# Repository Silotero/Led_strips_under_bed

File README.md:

# Led_strips_under_bed
Led strips that lights up according to the output of distance sensors.

The project uses 8 of HC-SR04 ultrasonic distance sensors to measure the distance beetween a detected project. They are separated into 2 zones, 4 sensors each. The 2 zones are at a 90 deegre angle (on a corner). Appropriate leds on the 2 led strips light up according to the readout of the sensors. There are 4 zones according to the distance:
-more than 115 cm - nothing lights up
-beetween 85 cm and 115 cm - light up blue
-beetween 55 cm and 85 cm - light up green
-beetween 22 cm and 55 cm - light up red

Everything is controlled via Atmega328p. The led strips are of WS2813 type.

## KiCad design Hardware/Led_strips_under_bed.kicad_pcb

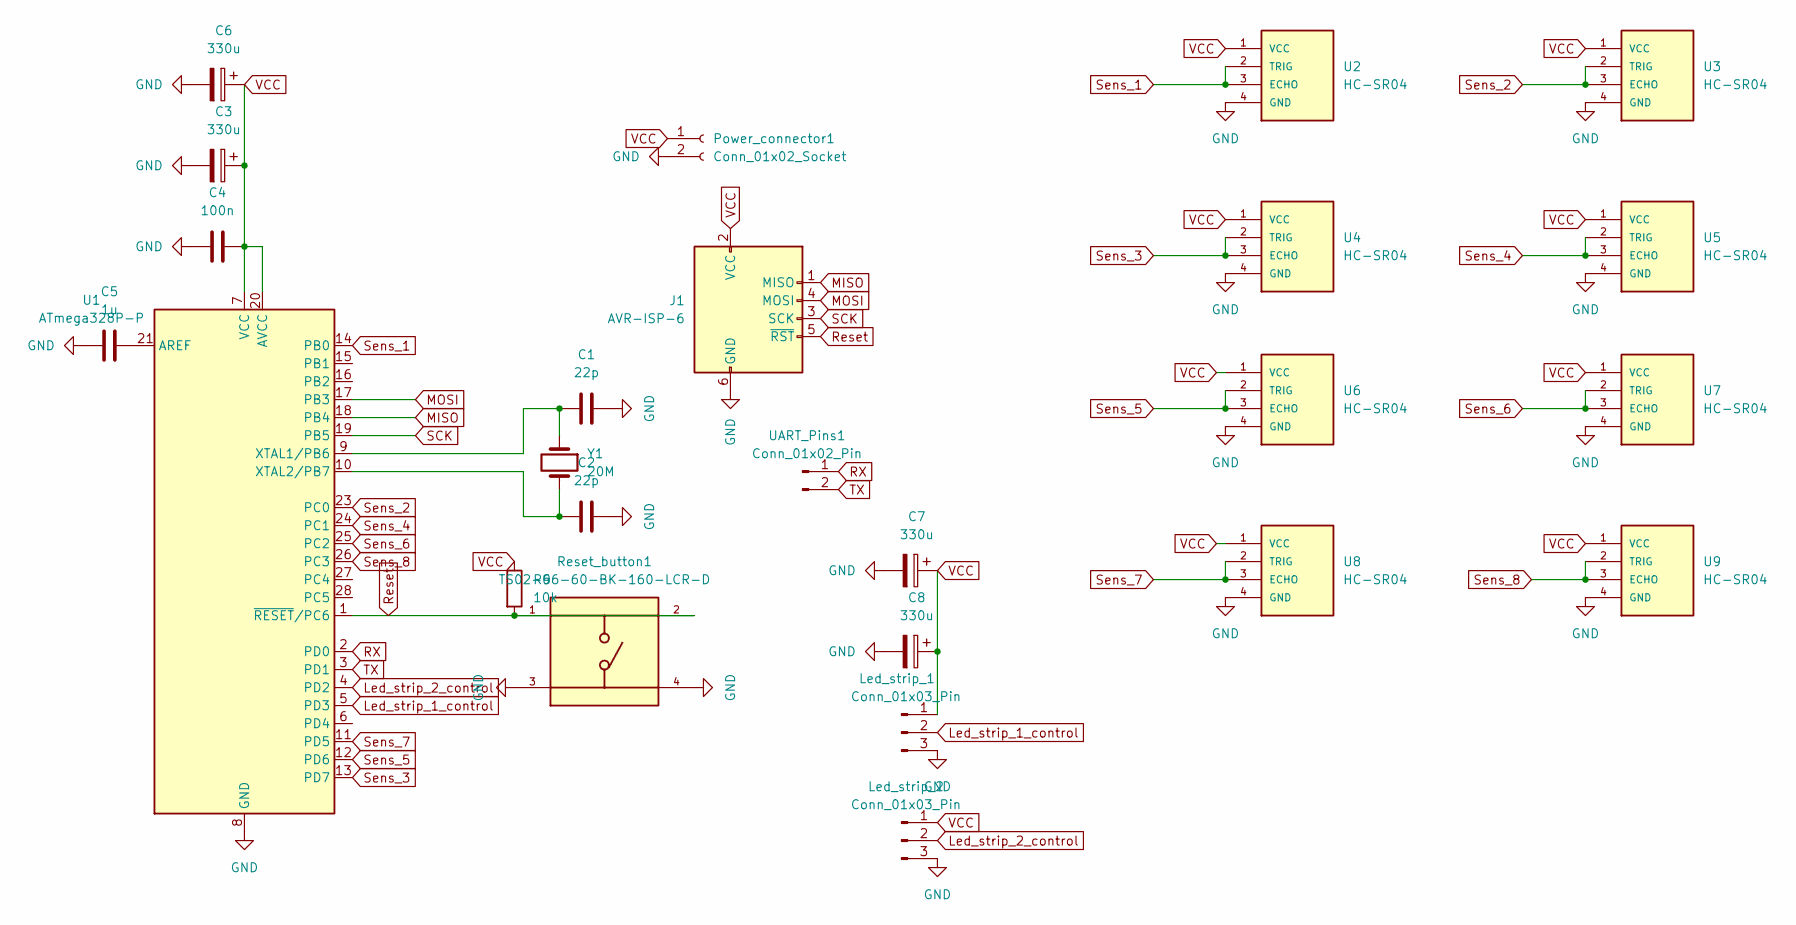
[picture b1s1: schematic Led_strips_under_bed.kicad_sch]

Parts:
C1, C2: 22p; C_0603_1608Metric
C3, C6, C7, C8: 330u; CP_Radial_D6.3mm_P2.50mm
C4: 100n; C_0603_1608Metric
C5: 1u; C_0603_1608Metric
J1: AVR-ISP-6; IDC-Header_2x03_P2.54mm_Vertical
Led_strip_1, Led_strip_2: Conn_01x03_Pin; PinHeader_1x03_P2.54mm_Vertical
Power_connector1: Conn_01x02_Socket; PinSocket_1x02_P2.54mm_Vertical
R9: 10k; R_0805_2012Metric
Reset_button1: TS02-66-60-BK-160-LCR-D; SW_TS02-66-60-BK-160-LCR-D; PARTREV 1.0
U1: ATmega328P-P; DIP-28_W7.62mm
U2, U3, U4, U5, U6, U7, U8, U9: HC-SR04; XCVR_HC-SR04
UART_Pins1: Conn_01x02_Pin; PinHeader_1x02_P2.54mm_Vertical
Y1: 20M; Resonator-2Pin_W7.0mm_H2.5mm

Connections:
GND: C1.2, C2.2, C3.2, C4.2, C5.2, C6.2, C7.2, C8.2, J1.6 (GND), Led_strip_1.3, Led_strip_2.3, Power_connector1.2, Reset_button1.3, Reset_button1.4, U1.8 (GND), U1.22 (GND), U2.4 (GND), U3.4 (GND), U4.4 (GND), U5.4 (GND), U6.4 (GND), U7.4 (GND), U8.4 (GND), U9.4 (GND); also elsewhere on the board
Led_strip_1_control: Led_strip_1.2, U1.5 (PD3)
Led_strip_2_control: Led_strip_2.2, U1.4 (PD2)
MISO: J1.1 (MISO), U1.18 (PB4)
MOSI: J1.4 (MOSI), U1.17 (PB3)
unnamed: C5.1, U1.21 (AREF)
unnamed: C1.1, U1.9 (XTAL1/PB6), Y1.1
unnamed: C2.1, U1.10 (XTAL2/PB7), Y1.2
RX: U1.2 (PD0), UART_Pins1.1
Reset: J1.5 (~RST), R9.2, Reset_button1.1, Reset_button1.2, U1.1 (~RESET/PC6); also elsewhere on the board
SCK: J1.3 (SCK), U1.19 (PB5)
Sens_1: U1.14 (PB0), U2.2 (TRIG), U2.3 (ECHO)
Sens_2: U1.23 (PC0), U3.2 (TRIG), U3.3 (ECHO)
Sens_3: U1.13 (PD7), U4.2 (TRIG), U4.3 (ECHO)
Sens_4: U1.24 (PC1), U5.2 (TRIG), U5.3 (ECHO)
Sens_5: U1.12 (PD6), U6.2 (TRIG), U6.3 (ECHO)
Sens_6: U1.25 (PC2), U7.2 (TRIG), U7.3 (ECHO)
Sens_7: U1.11 (PD5), U8.2 (TRIG), U8.3 (ECHO)
Sens_8: U1.26 (PC3), U9.2 (TRIG), U9.3 (ECHO)
TX: U1.3 (PD1), UART_Pins1.2
VCC: C3.1, C4.1, C6.1, C7.1, C8.1, J1.2 (VCC), Led_strip_1.1, Led_strip_2.1, Power_connector1.1, R9.1, U1.7 (VCC), U1.20 (AVCC), U2.1 (VCC), U3.1 (VCC), U4.1 (VCC), U5.1 (VCC), U6.1 (VCC), U7.1 (VCC), U8.1 (VCC), U9.1 (VCC)

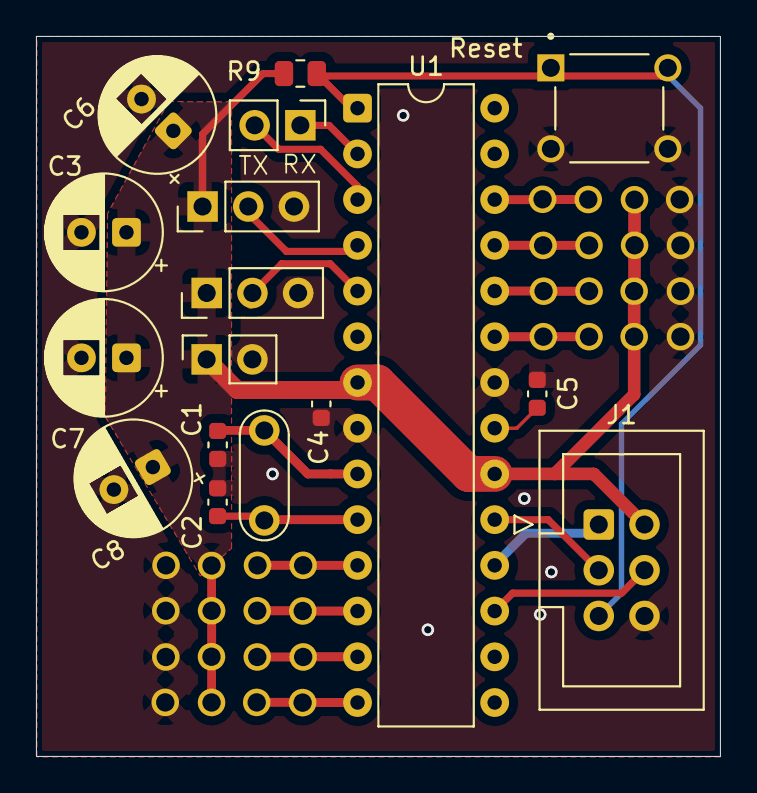
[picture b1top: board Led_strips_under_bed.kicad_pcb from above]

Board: 2 copper layers, 38.0 x 40.0 mm, 25 parts (0 on the bottom side), 21 nets.

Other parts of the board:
Reset: TS02-66-60-BK-160-LCR-D; SW_TS02-66-60-BK-160-LCR-D

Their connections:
GND: Reset.3, Reset.4; also elsewhere on the board
Reset: Reset.1, Reset.2; also elsewhere on the board

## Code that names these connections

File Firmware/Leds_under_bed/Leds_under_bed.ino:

#ifndef F_CPU
#define F_CPU 20000000UL
#endif
#include <avr/io.h>
#include <util/delay.h>
#include <stdbool.h>
#include <FastLED.h>
#include <UART_w_c.h>
#include <stdio.h>

#define NUM_LEDS 60 // number of used leds
#define DATA_PIN_STRIP_1 2 // pin for the led strip control
#define DATA_PIN_STRIP_2 3 // pin for the led strip control
#define NUM_SENSORS 8 // number of used distance sensors
#define MAX_DIST 200  // cm
#define CHIPSET WS2813
#define COLOR_ORDER BRG

#define CPU_FREQUENCY 20000000UL
#define BAUDRATE 9600

#define DEBUG 0

#if DEBUG
    #define DEBUG_uart_putchar (x) uart_putchar(x)
#endif

CRGB leds1[NUM_LEDS]; // array for holding values for the leds
CRGB leds2[NUM_LEDS]; // array for holding values for the leds

typedef struct {
    volatile uint8_t *ddr;
    volatile uint8_t *port;
    volatile uint8_t *pinx;
    uint8_t pin;
} Sensor_Pin;

const Sensor_Pin sensor_pins[] = {
    { &DDRD, &PORTD, &PIND, PD5 },
    { &DDRD, &PORTD, &PIND, PD6 },
    { &DDRD, &PORTD, &PIND, PD7 },
    { &DDRB, &PORTB, &PINB, PB0 },
    { &DDRC, &PORTC, &PINC, PC0 },
    { &DDRC, &PORTC, &PINC, PC1 },
    { &DDRC, &PORTC, &PINC, PC2 },
    { &DDRC, &PORTC, &PINC, PC3 },
};

long distances[NUM_SENSORS];
uint8_t counter = 0;

void timer1_init(void) {
    TCCR1A = 0;               // Normal mode
    TCCR1B = (1 << CS11);     // Prescaler 8 → 1 tick = 0.5 us @ 16 MHz, 1 us @ 8 MHz, 0,4 us @ 20 MHz
    TCNT1 = 0;                // Reset counter
}

long readDistance(volatile uint8_t *ddr, volatile uint8_t *port_out, volatile uint8_t *pinx_in, uint8_t pin) {
    // Set pin as output to send TRIG
    *ddr |= (1 << pin);       // Output
    *port_out &= ~(1 << pin);     // LOW
    _delay_us(2);
    *port_out |= (1 << pin);      // HIGH for 10us
    _delay_us(10);
    *port_out &= ~(1 << pin);     // LOW

    // Set pin as input to receive ECHO
    *ddr &= ~(1 << pin);      // Input
    *port_out &= ~(1 << pin);

    uint32_t counter = 0;
    while(!(*pinx_in & (1 << pin))) {   // Wait for pin to be high, meaning echo has started
        if(counter++ > 10000) return 0; 
    }
    TCNT1=0; // reset counter
    while(*pinx_in & (1<< pin)) {  // wait while pin is high meaning echo is still sending
        if(TCNT1 > 40000) break; // Max distance timeout
    }
    long duration= TCNT1; // read counter after echo has ended

    long distance = duration / 146; // = 0.034 speed of sound / 2 divide by 2 cause travel forth and back * 0.4 timing with the prescaler to get 1 us Convert echo duration to cm
    return distance;
}
void setup() {
    timer1_init();
    uart_init(CPU_FREQUENCY, BAUDRATE);
    FastLED.addLeds<CHIPSET, DATA_PIN_STRIP_1, COLOR_ORDER>(leds1, NUM_LEDS);
    FastLED.addLeds<CHIPSET, DATA_PIN_STRIP_2, COLOR_ORDER>(leds2, NUM_LEDS);
    FastLED.setBrightness(100);
}

void loop() {
    counter++;
    if (counter % 10 == 0) {
        FastLED.clear();
    }
    for (int i = 0; i < NUM_SENSORS; i++) {
        long combined_distance = 0;
        for (int j = 0; j < 3; j++) {
            combined_distance += readDistance(sensor_pins[i].ddr, sensor_pins[i].port, sensor_pins[i].pinx, sensor_pins[i].pin);
            _delay_ms(80);
        }
        distances[i] = combined_distance / 2;
        distances[i] = constrain(distances[i], 0, MAX_DIST);
        #if DEBUG
            char buffer[16];
            snprintf(buffer, sizeof(buffer), "%ld\n", distances[i]);
            for (char *p = buffer; *p; p++) {
                uart_putchar(*p);
            }
            uart_putchar('c');
            uart_putchar('m');
        #endif
        if (i < 4) {
            if (distances[i] < 55 && distances[i] > 22) {
                for (int j= 0; j < 15; j++) {
                leds1[i*15+j] =  CRGB::Red;
                }
            }
            else if (distances[i] < 85) {
                for (int j = 0; j < 15; j++) {
                leds1[i*15+j] =  CRGB::Green;
                }
            }
            else if (distances[i] < 115) {
                for (int j = 0; j < 15; j++) {
                leds1[i*15+j] =  CRGB::Blue;
                }
            }
        }
        else {
            if (distances[i] < 55 && distances[i] > 22) {
                for (int j = 0; j < 15; j++) {
                leds2[(i-4)*15+j] =  CRGB::Red;
                }
            }
            else if (distances[i] < 85) {
                for (int j = 0; j < 15; j++) {
                leds2[(i-4)*15+j] =  CRGB::Green;
                }
            }
            else if (distances[i] < 115) {
                for (int j = 0; j < 15; j++) {
                leds2[(i-4)*15+j] =  CRGB::Blue;
                }
            }
        }
        FastLED.show();
    }
}

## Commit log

2026-04-06 Update .gitignore
    Dodano ignorowanie folderów backups oraz gerber
2026-04-06 Finished project
2026-04-07 Update README.md
    Added the type of led strips (WS2813)
2026-04-07 Changed firmware file structure
